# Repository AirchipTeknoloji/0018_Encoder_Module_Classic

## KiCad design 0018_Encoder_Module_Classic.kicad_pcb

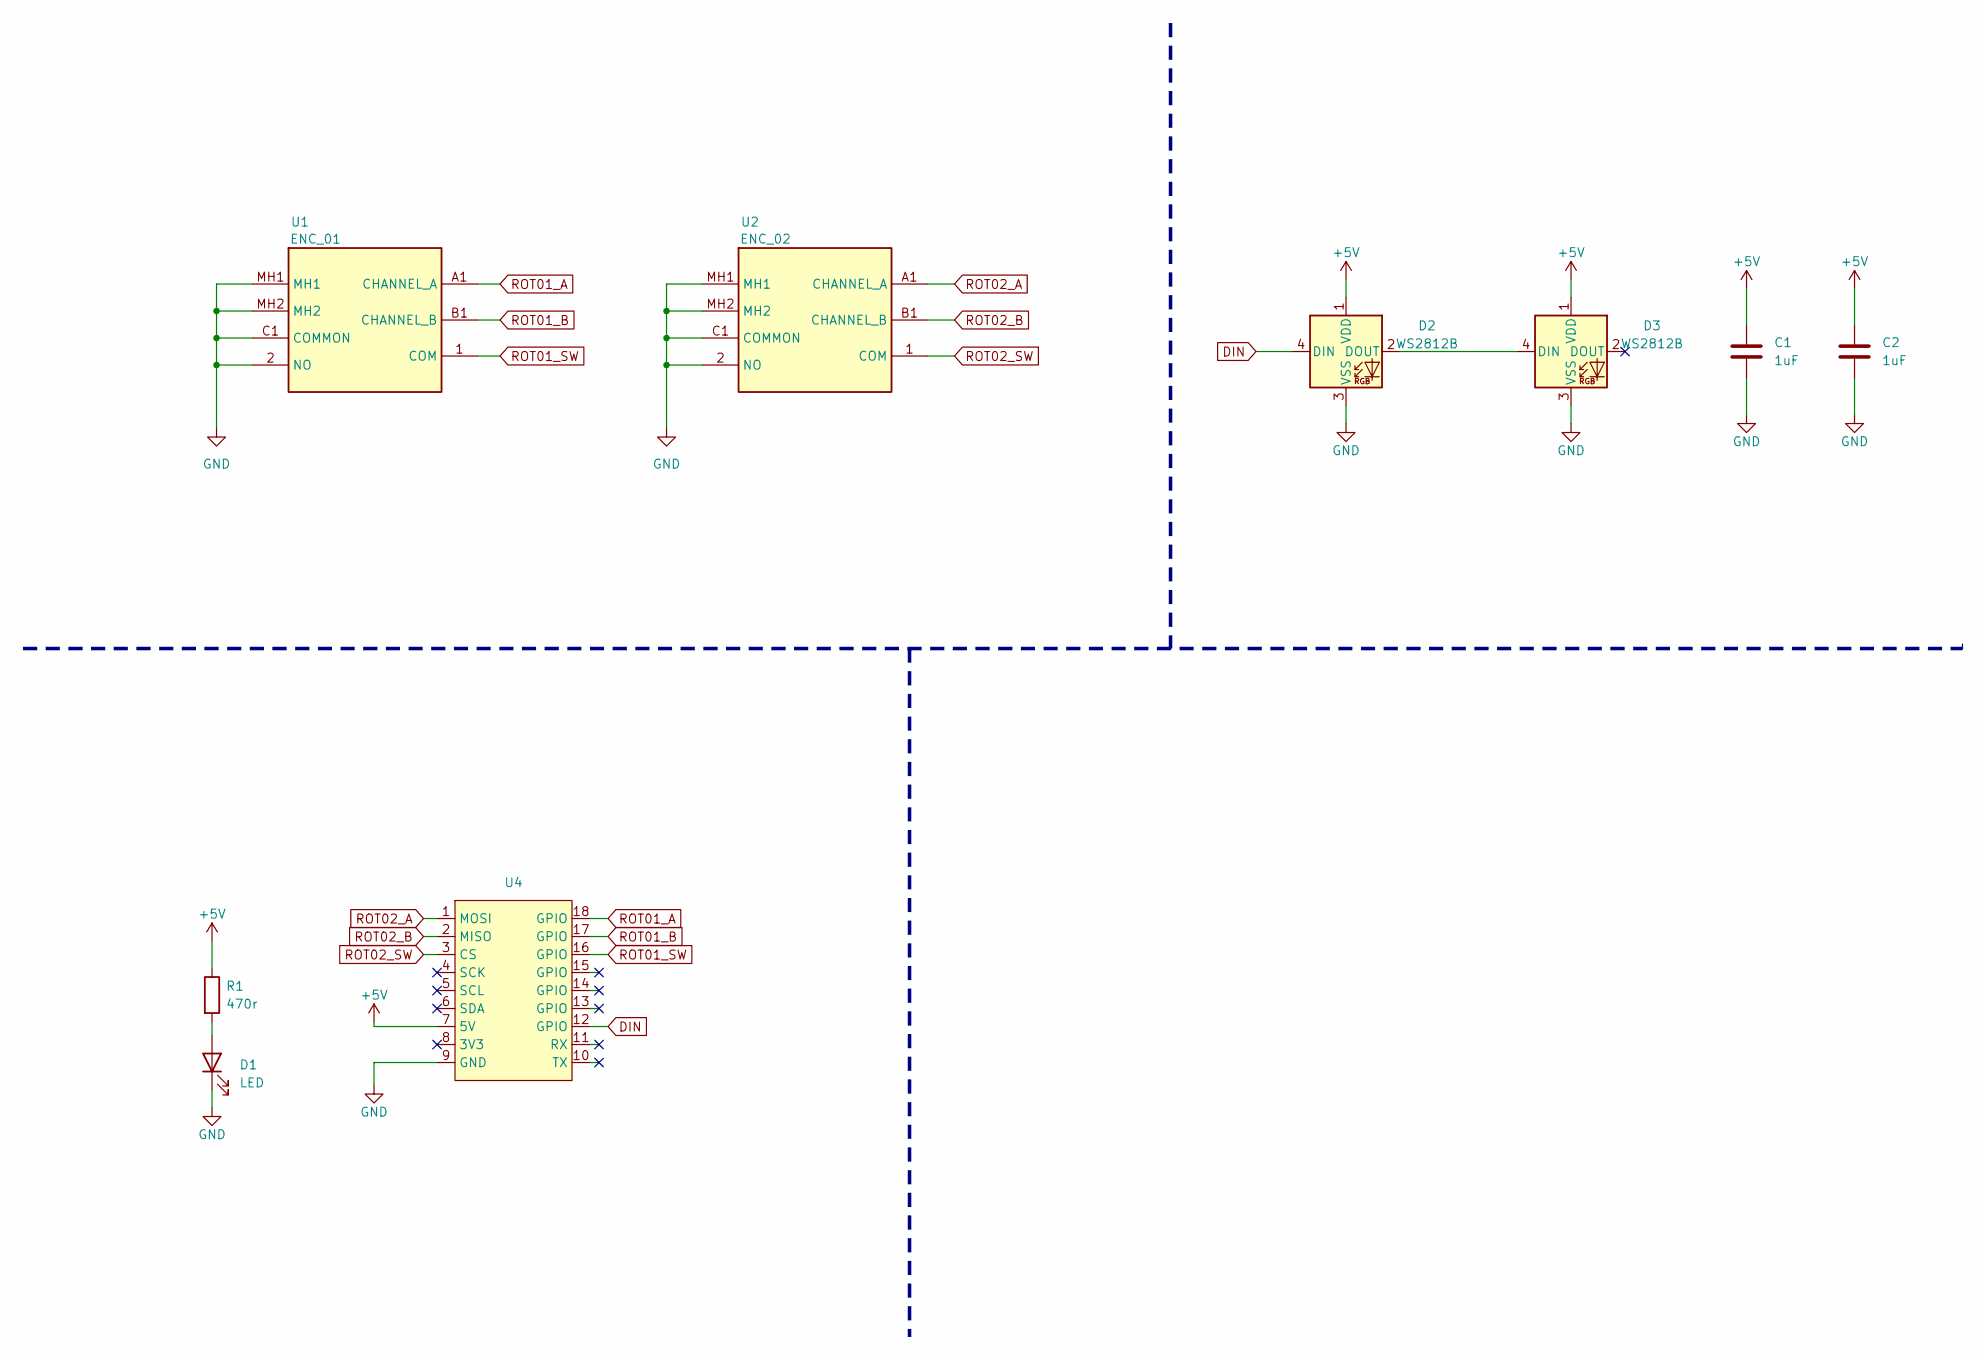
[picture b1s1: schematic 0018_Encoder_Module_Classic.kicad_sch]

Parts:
C1, C2: 1uF; C_0603_1608Metric
D1: LED; LED_0805_2012Metric
D2, D3: WS2812B; LED_WS2812B_PLCC4_5.0x5.0mm_P3.2mm
R1: 470r; R_0603_1608Metric
U1: ENC_01; PEC11R4215FS0024; Mouser Part Number 652-PEC11R-4215F-S24
U2: ENC_02; PEC11R4215FS0024; Mouser Part Number 652-PEC11R-4215F-S24
U4: air__module

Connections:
+5V: C1.1, C2.1, D2.1 (VDD), D3.1 (VDD), R1.1, U4.7 (5V)
DIN: D2.4 (DIN), U4.12 (GPIO)
GND: C1.2, C2.2, D1.1 (K), D2.3 (VSS), D3.3 (VSS), U1.2 (NO), U1.C1 (COMMON), U1.MH1, U1.MH2, U2.2 (NO), U2.C1 (COMMON), U2.MH1, U2.MH2, U4.9 (GND)
unnamed: D1.2 (A), R1.2
unnamed: D2.2 (DOUT), D3.4 (DIN)
ROT01_A: U1.A1 (CHANNEL_A), U4.18 (GPIO)
ROT01_B: U1.B1 (CHANNEL_B), U4.17 (GPIO)
ROT01_SW: U1.1 (COM), U4.16 (GPIO)
ROT02_A: U2.A1 (CHANNEL_A), U4.1 (MOSI)
ROT02_B: U2.B1 (CHANNEL_B), U4.2 (MISO)
ROT02_SW: U2.1 (COM), U4.3 (CS)

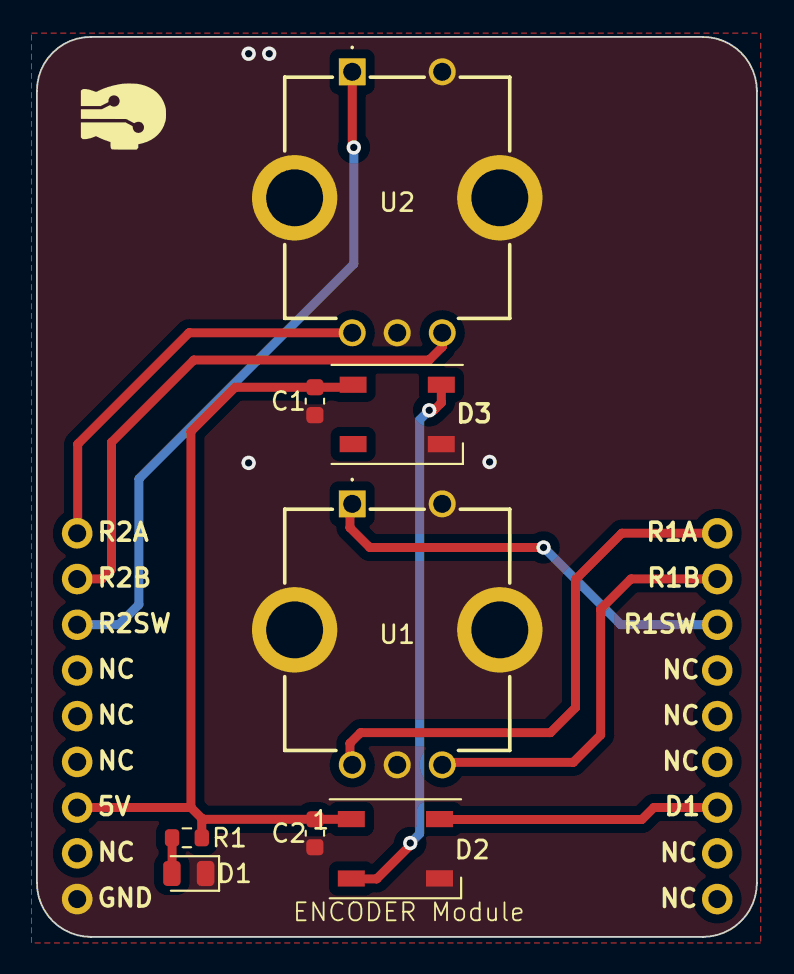
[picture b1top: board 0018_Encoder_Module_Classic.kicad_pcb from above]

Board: 2 copper layers, 40.0 x 50.0 mm, 9 parts (0 on the bottom side), 11 nets.
